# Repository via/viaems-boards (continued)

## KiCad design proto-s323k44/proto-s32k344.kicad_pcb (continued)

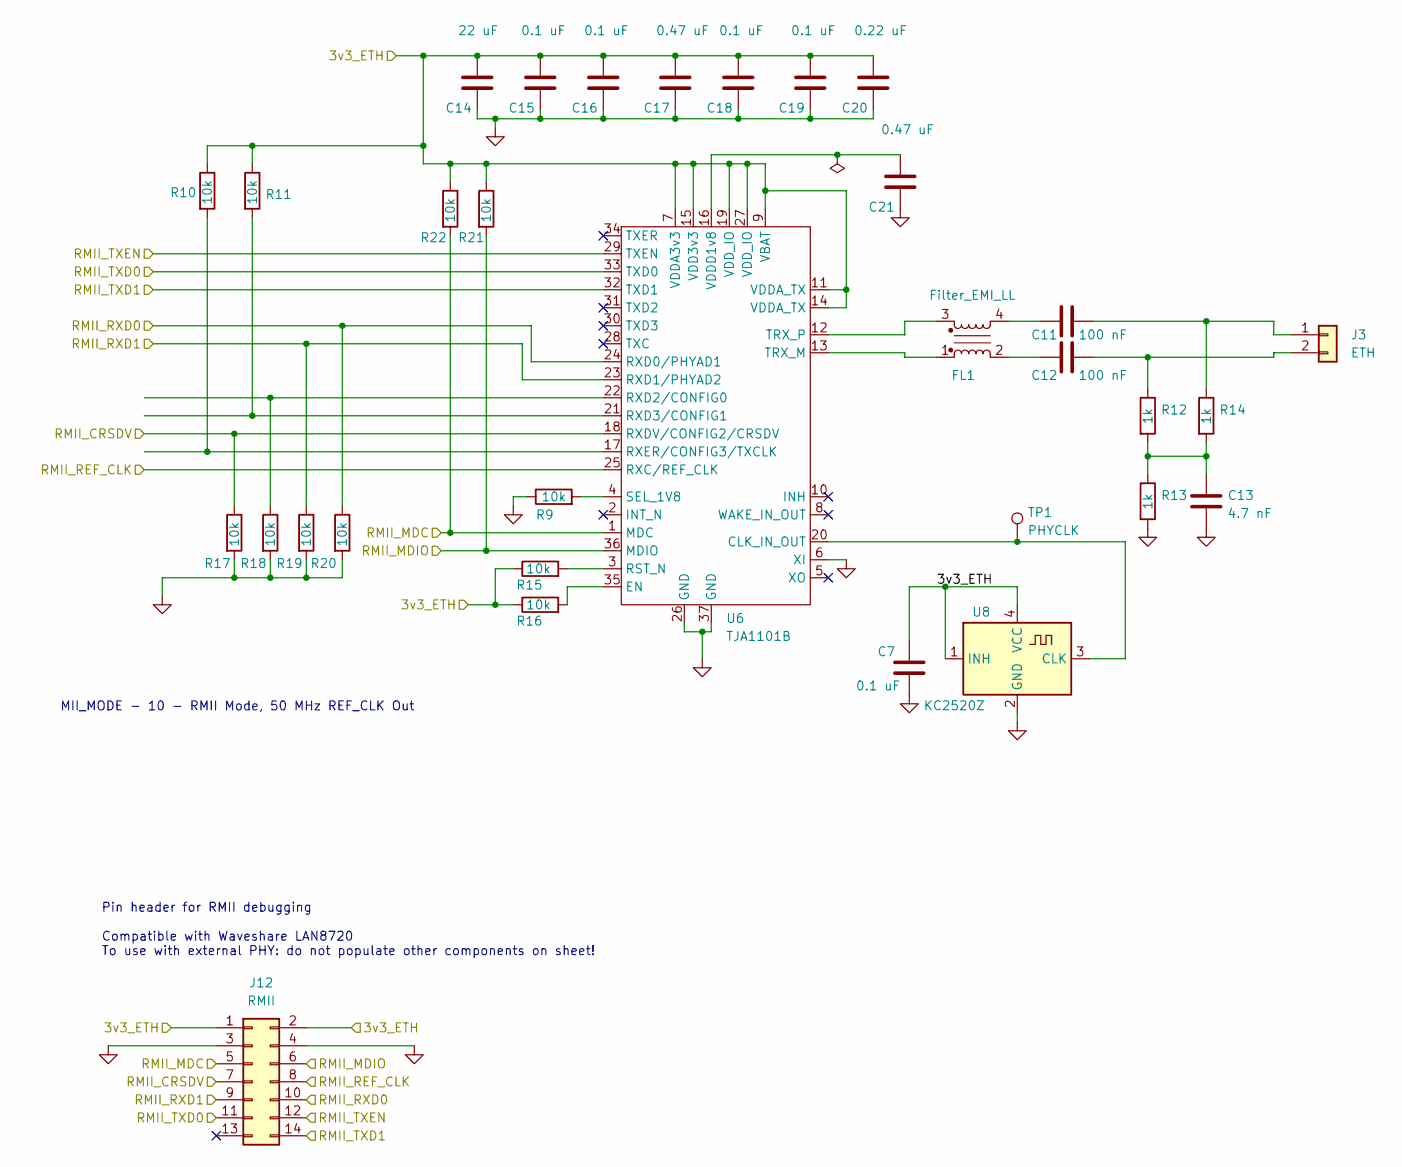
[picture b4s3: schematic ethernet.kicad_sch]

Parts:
C7, C15, C16, C18, C19: 0.1 uF; C_0805_2012Metric
C11, C12: 100 nF; C_0805_2012Metric
C13: 4.7 nF; C_0805_2012Metric
C14: 22 uF; C_0805_2012Metric
C17, C21: 0.47 uF; C_0805_2012Metric
C20: 0.22 uF; C_0805_2012Metric
FL1: Filter_EMI_LL; DLW43_MUR; Digikey-Part DLW43MH201XK2L
J3: ETH; PinHeader_1x02_P2.54mm_Vertical
J12: RMII; PinHeader_2x07_P2.54mm_Vertical
R9, R10, R11, R15, R16, R17, R18, R19, R20, R21, R22: 10k; R_0805_2012Metric
R12, R13, R14: 1k; R_0805_2012Metric
TP1: PHYCLK; TestPoint_Pad_D1.5mm
U6: TJA1101B; QFN-36-1EP_6x6mm_P0.5mm_EP3.7x3.7mm
U8: KC2520Z; Oscillator_SMD_Kyocera_KC2520Z-4Pin_2.5x2.0mm

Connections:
/3v3: C7.1, C14.1, C15.1, C16.1, C17.1, C18.1, C19.1, C20.1, J12.1, J12.2, R10.1, R11.1, R15.1, R16.1, R21.1, R22.1, U6.7 (VDDA3v3), U6.9 (VBAT), U6.11 (VDDA_TX), U6.14 (VDDA_TX), U6.15 (VDD3v3), U6.19 (VDD_IO), U6.27 (VDD_IO), U8.1 (INH), U8.4 (VCC); also elsewhere on the board
/PTB4: J12.14, U6.32 (TXD1); also elsewhere on the board
/PTB5: J12.11, U6.33 (TXD0); also elsewhere on the board
/PTC0: J12.10, R20.1, U6.24 (RXD0/PHYAD1); also elsewhere on the board
/PTC1: J12.9, R19.1, U6.23 (RXD1/PHYAD2); also elsewhere on the board
/PTC17: J12.7, R17.1, U6.18 (RXDV/CONFIG2/CRSDV); also elsewhere on the board
/PTD6: J12.8, U6.25 (RXC/REF_CLK); also elsewhere on the board
/PTD16: J12.6, R21.2, U6.36 (MDIO); also elsewhere on the board
/PTE8: J12.5, R22.2, U6.1 (MDC); also elsewhere on the board
/PTE9: J12.12, U6.29 (TXEN); also elsewhere on the board
GND: C7.2, C13.2, C14.2, C15.2, C16.2, C17.2, C18.2, C19.2, C20.2, C21.2, J12.3, J12.4, R9.1, R13.2, R17.2, R18.2, R19.2, R20.2, U6.6 (XI), U6.26 (GND), U6.37 (GND), U8.2 (GND); also elsewhere on the board
unnamed: C11.1, FL1.4
unnamed: C12.1, FL1.2
unnamed: C13.1, R12.2, R13.1, R14.2
unnamed: C11.2, J3.1, R14.1
unnamed: C12.2, J3.2, R12.1
unnamed: TP1.1, U6.20 (CLK_IN_OUT), U8.3 (CLK)
unnamed: R16.2, U6.35 (EN)
unnamed: R15.2, U6.3 (RST_N)
unnamed: R18.1, U6.22 (RXD2/CONFIG0)
unnamed: R11.2, U6.21 (RXD3/CONFIG1)
unnamed: R10.2, U6.17 (RXER/CONFIG3/TXCLK)
unnamed: R9.2, U6.4 (SEL_1V8)
unnamed: FL1.1, U6.13 (TRX_M)
unnamed: FL1.3, U6.12 (TRX_P)
unnamed: C21.1, U6.16 (VDDD1v8)

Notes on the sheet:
MII_MODE - 10 - RMII Mode, 50 MHz REF_CLK Out
Pin header for RMII debugging Compatible with Waveshare LAN8720 To use with external PHY: do not populate other components on sheet!

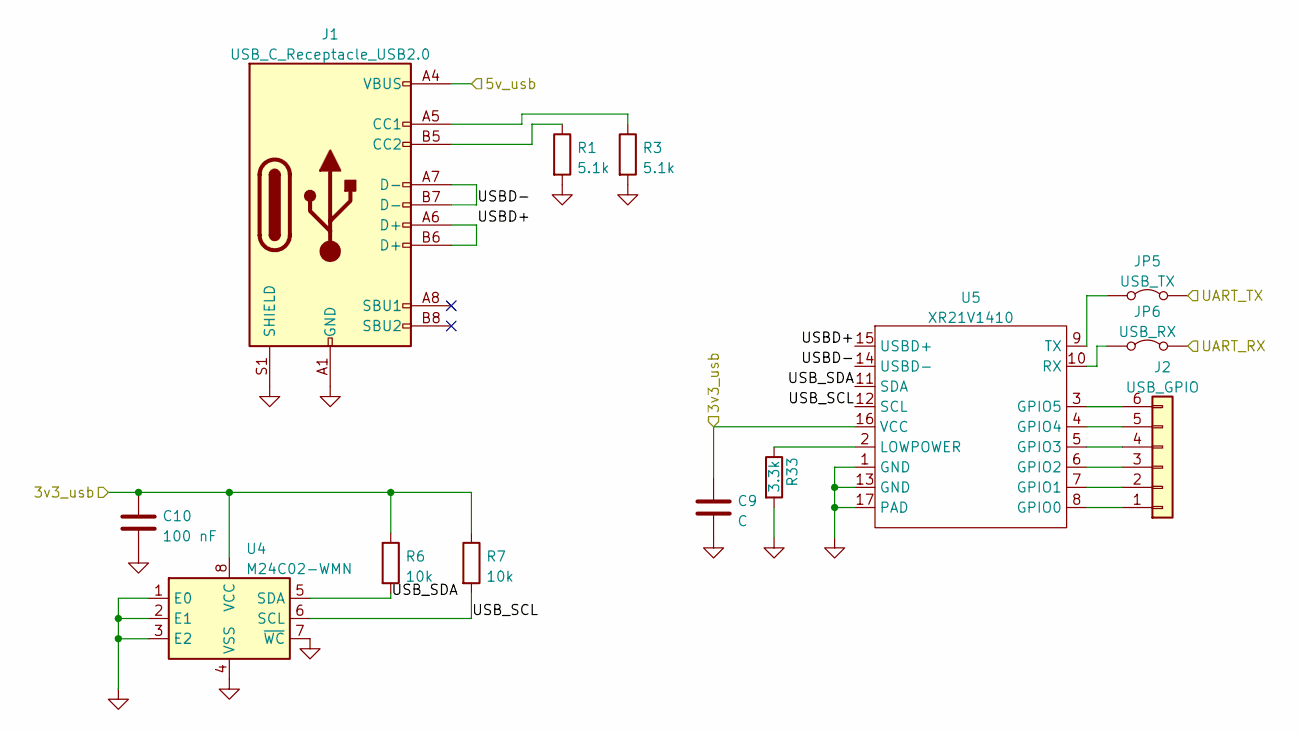
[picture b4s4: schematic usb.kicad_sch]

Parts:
C9: C; C_0805_2012Metric
C10: 100 nF; C_0805_2012Metric
J1: USB_C_Receptacle_USB2.0; USB_C_Receptacle_GCT_USB4105-xx-A_16P_TopMnt_Horizontal
J2: USB_GPIO; PinHeader_2x03_P2.54mm_Vertical
JP5: USB_TX; PinHeader_1x02_P2.54mm_Vertical
JP6: USB_RX; PinHeader_1x02_P2.54mm_Vertical
R1, R3: 5.1k; R_0805_2012Metric
R6, R7: 10k; R_0805_2012Metric
R33: 3.3k; R_0805_2012Metric
U4: M24C02-WMN; SOIC-8_3.9x4.9mm_P1.27mm
U5: XR21V1410; QFN-16-1EP_3x3mm_P0.5mm_EP1.7x1.7mm

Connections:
/3v3: C9.1, C10.1, R6.1, R7.1, U4.8 (VCC), U5.16 (VCC); also elsewhere on the board
/5v_usb: J1.A4 (VBUS), J1.A9 (VBUS), J1.B4 (VBUS), J1.B9 (VBUS); also elsewhere on the board
/PTC15: JP5.2 (B); also elsewhere on the board
/PTC16: JP6.2 (B); also elsewhere on the board
/USB/USBD+: J1.A6 (D+), J1.B6 (D+), U5.15 (USBD+)
/USB/USBD-: J1.A7 (D-), J1.B7 (D-), U5.14 (USBD-)
/USB/USB_SCL: R7.2, U4.6 (SCL), U5.12 (SCL)
/USB/USB_SDA: R6.2, U4.5 (SDA), U5.11 (SDA)
GND: C9.2, C10.2, J1.A1 (GND), J1.A12 (GND), J1.B1 (GND), J1.B12 (GND), J1.S1 (SHIELD), R1.2, R3.2, R33.2, U4.1 (E0), U4.2 (E1), U4.3 (E2), U4.4 (VSS), U4.7 (~WC), U5.1 (GND), U5.13 (GND), U5.17 (PAD); also elsewhere on the board
unnamed: J1.A5 (CC1), R3.1
unnamed: J1.B5 (CC2), R1.1
unnamed: J2.1, U5.8 (GPIO0)
unnamed: J2.2, U5.7 (GPIO1)
unnamed: J2.3, U5.6 (GPIO2)
unnamed: J2.4, U5.5 (GPIO3)
unnamed: J2.5, U5.4 (GPIO4)
unnamed: J2.6, U5.3 (GPIO5)
unnamed: JP5.1 (A), U5.9 (TX)
unnamed: JP6.1 (A), U5.10 (RX)
unnamed: R33.1, U5.2 (LOWPOWER)

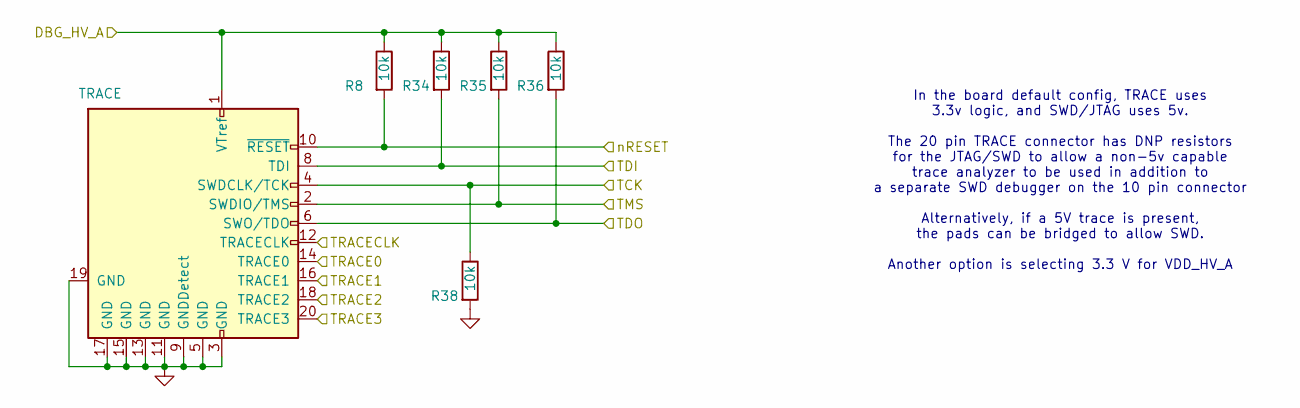
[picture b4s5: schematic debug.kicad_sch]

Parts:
J13: TRACE; PinSocket_2x10_P1.27mm_Vertical_SMD
R8, R34, R35, R36, R38: 10k; R_0805_2012Metric

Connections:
/PTA4: J13.2 (SWDIO/TMS), R35.2; also elsewhere on the board
/PTA5: J13.10 (~RESET), R8.2; also elsewhere on the board
/PTA10: J13.6 (SWO/TDO), R36.2; also elsewhere on the board
/PTC2: J13.12 (TRACECLK); also elsewhere on the board
/PTC4: J13.4 (SWDCLK/TCK), R38.1; also elsewhere on the board
/PTC5: J13.8 (TDI), R34.2; also elsewhere on the board
/PTD7: J13.14 (TRACE0); also elsewhere on the board
/PTD10: J13.20 (TRACE3); also elsewhere on the board
/PTD11: J13.18 (TRACE2); also elsewhere on the board
/PTD12: J13.16 (TRACE1); also elsewhere on the board
/VDD_HV_A: J13.1 (VTref), R8.1, R34.1, R35.1, R36.1; also elsewhere on the board
GND: J13.3 (GND), J13.5 (GND), J13.9 (GNDDetect), J13.11 (GND), J13.13 (GND), J13.15 (GND), J13.17 (GND), J13.19 (GND), R38.2; also elsewhere on the board

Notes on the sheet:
In the board default config, TRACE uses 3.3v logic, and SWD/JTAG uses 5v. The 20 pin TRACE connector has DNP resistors for the JTAG/SWD to allow a non-5v capable trace analyzer to be used in addition to a separate SWD debugger on the 10 pin connector Alternatively, if a 5V trace is present, the pad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

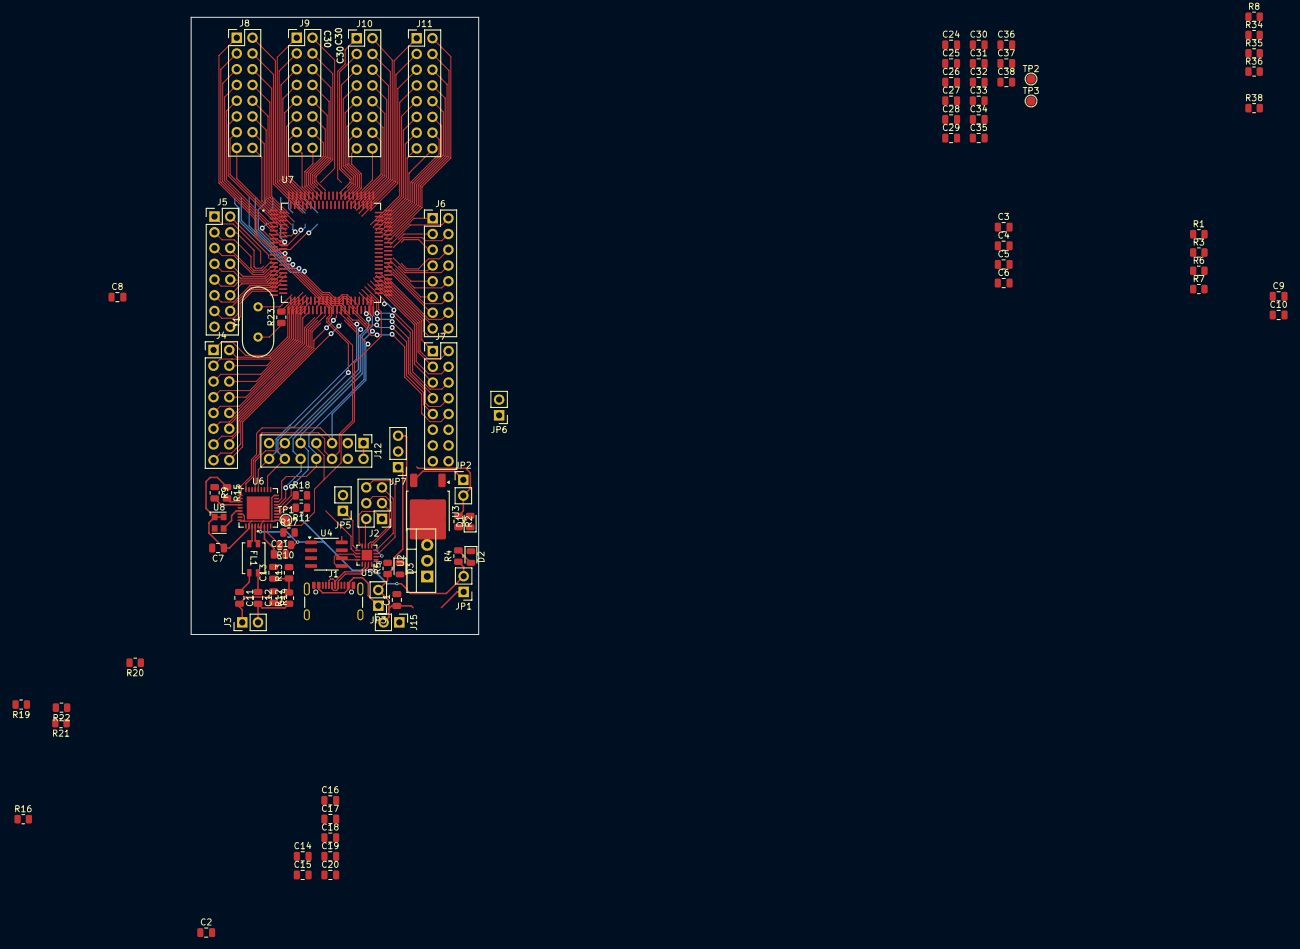
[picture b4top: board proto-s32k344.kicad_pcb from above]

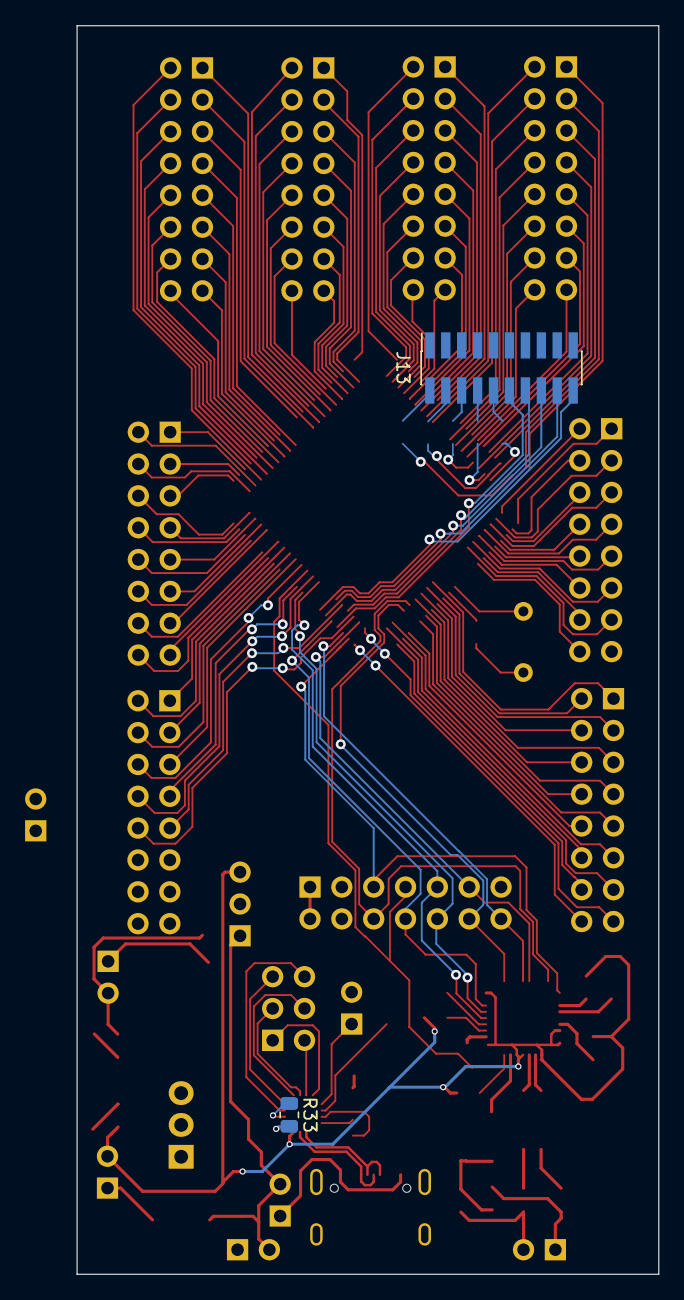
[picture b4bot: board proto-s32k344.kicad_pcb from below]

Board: 2 copper layers, 46.4 x 99.6 mm, 99 parts (2 on the bottom side), 190 nets.

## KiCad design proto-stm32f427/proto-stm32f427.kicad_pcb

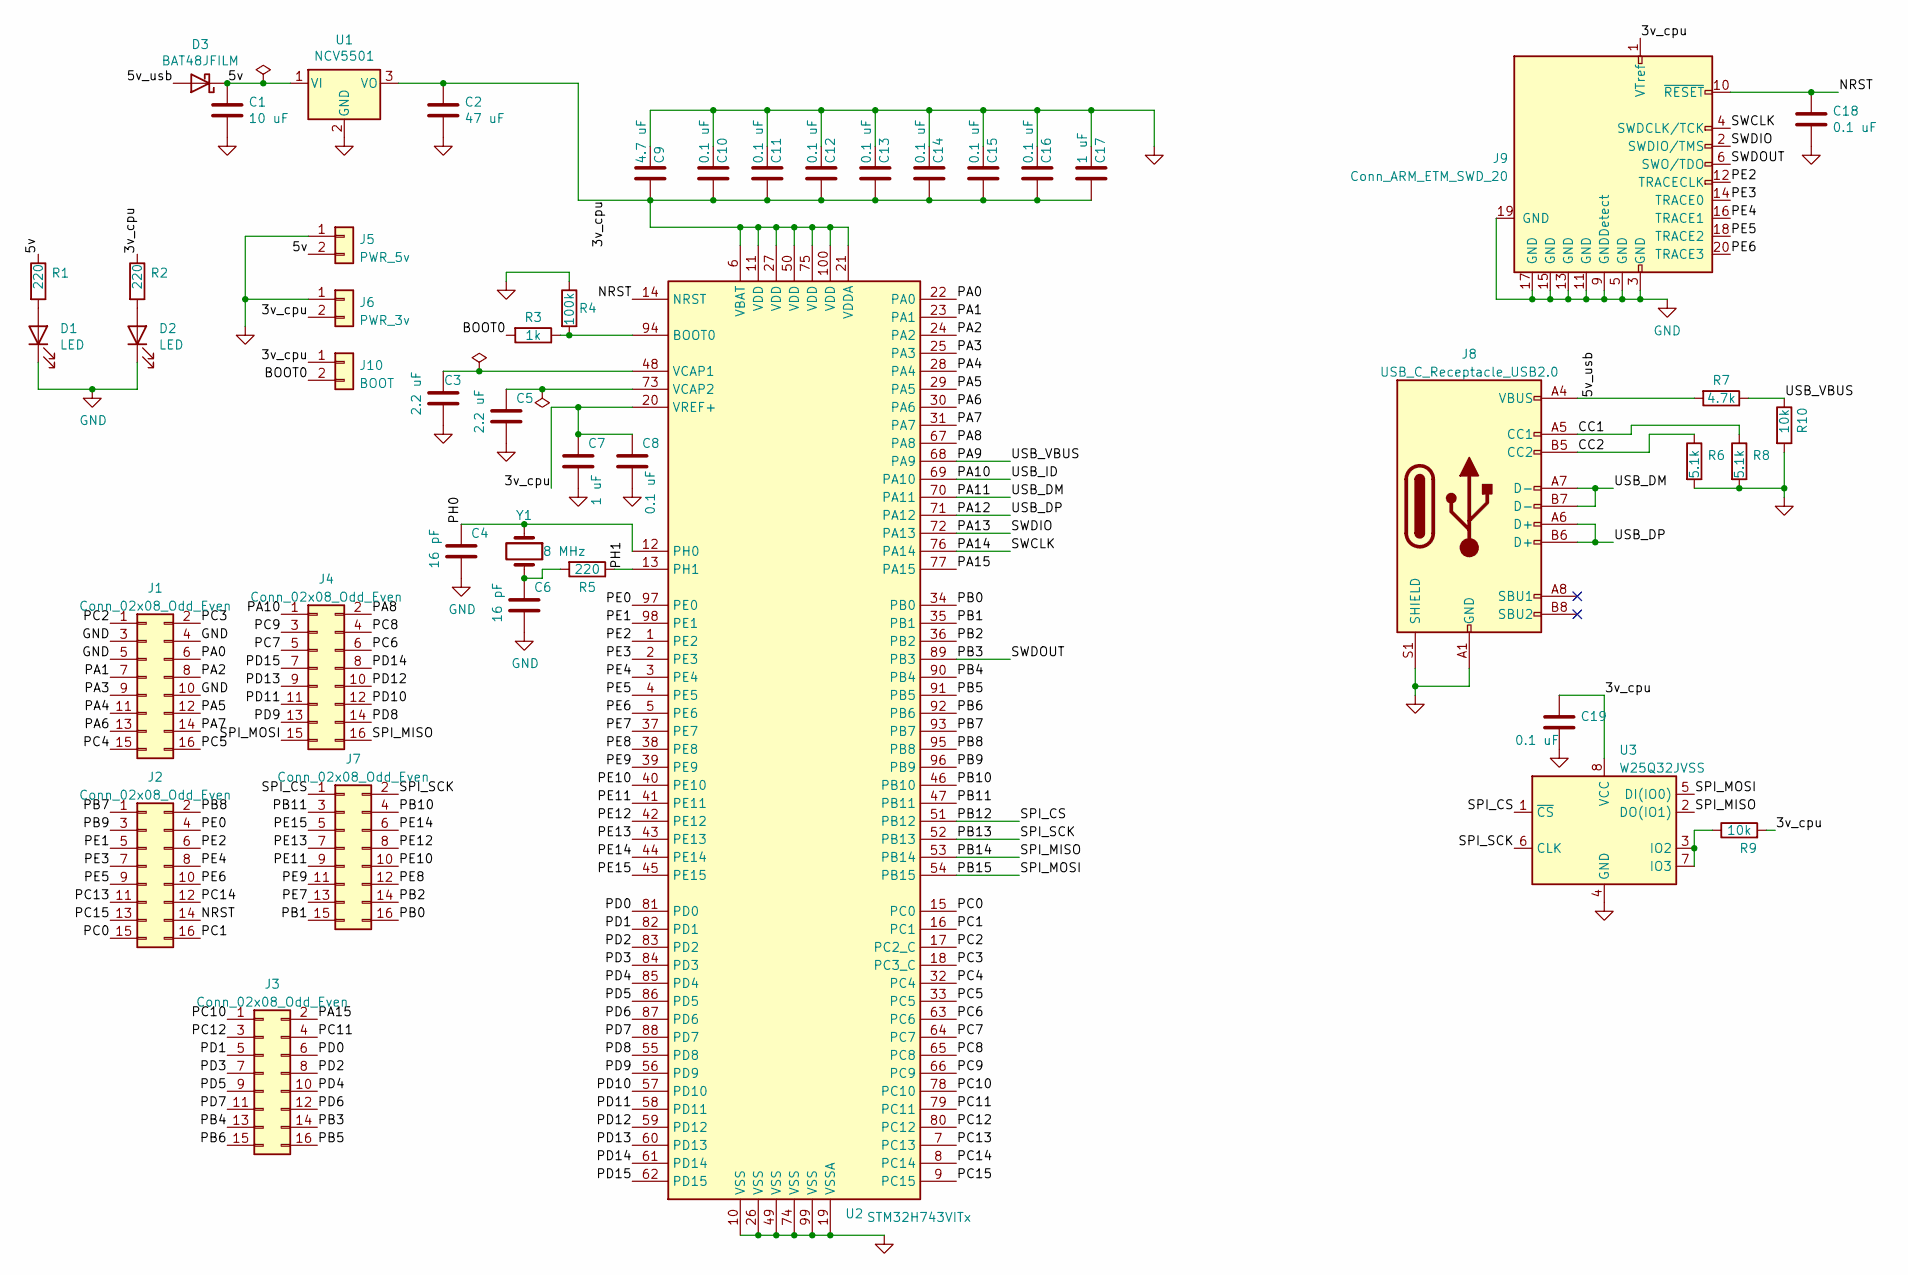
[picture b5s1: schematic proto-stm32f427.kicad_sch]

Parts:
C1: 10 uF; C_0805_2012Metric_Pad1.15x1.40mm_HandSolder; Digikey-Part 587-3417-1-ND
C2: 47 uF; C_0805_2012Metric_Pad1.15x1.40mm_HandSolder; Digikey-Part 718-1608-1-ND
C3, C5: 2.2 uF; C_0805_2012Metric_Pad1.15x1.40mm_HandSolder; Digikey-Part 1276-1188-1-ND
C4, C6: 16 pF; C_0805_2012Metric_Pad1.15x1.40mm_HandSolder; Digikey-Part 311-4228-1-ND
C7, C17: 1 uF; C_0805_2012Metric_Pad1.15x1.40mm_HandSolder; Digikey-Part 1276-1066-1-ND
C8, C10, C11, C12, C13, C14, C15, C16, C18: 0.1 uF; C_0805_2012Metric_Pad1.15x1.40mm_HandSolder; Digikey-Part 478-10836-1-ND
C9: 4.7 uF; C_0805_2012Metric_Pad1.15x1.40mm_HandSolder; Digikey-Part 445-14527-1-ND
C19: 0.1 uF; C_0805_2012Metric_Pad1.18x1.45mm_HandSolder
D1, D2: LED; LED_0805_2012Metric_Pad1.15x1.40mm_HandSolder; Digikey-Part 475-1415-1-ND
D3: BAT48JFILM; D_SOD-323_HandSoldering; Digikey-Part B0530WS-FDICT-ND
J1, J2, J3, J4, J7: Conn_02x08_Odd_Even; PinHeader_2x08_P2.54mm_Vertical
J5: PWR_5v; PinHeader_1x02_P2.54mm_Vertical
J6: PWR_3v; PinHeader_1x02_P2.54mm_Vertical
J8: USB_C_Receptacle_USB2.0; USB_C_Receptacle_GCT_USB4105-xx-A_16P_TopMnt_Horizontal; Digikey-Part 2073-USB4105-GF-ACT-ND
J9: Conn_ARM_ETM_SWD_20; PinHeader_2x10_P1.27mm_Vertical_SMD; Digikey-Part SAM9456-ND
J10: BOOT; PinHeader_1x02_P2.54mm_Vertical
R1, R2, R5: 220; R_0805_2012Metric_Pad1.20x1.40mm_HandSolder; Digikey-Part A129741CT-ND
R3: 1k; R_0805_2012Metric_Pad1.20x1.40mm_HandSolder; Digikey-Part RNCP0805FTD1K00CT-ND
R4: 100k; R_0805_2012Metric_Pad1.20x1.40mm_HandSolder; Digikey-Part P100KDACT-ND
R6, R8: 5.1k; R_0805_2012Metric_Pad1.20x1.40mm_HandSolder
R7: 4.7k; R_0805_2012Metric_Pad1.20x1.40mm_HandSolder; Digikey-Part 311-4.70KCRCT-ND
R9: 10k; R_0805_2012Metric_Pad1.20x1.40mm_HandSolder
R10: 10k; R_0805_2012Metric_Pad1.20x1.40mm_HandSolder; Digikey-Part RNCF0805DTE10K0CT-ND
U1: NCV5501; TO-252-2; Digikey-Part NCV5501DT33GOS-ND
U2: STM32H743VITx; LQFP-100_14x14mm_P0.5mm
U3: W25Q32JVSS; SOIC-8_5.23x5.23mm_P1.27mm
Y1: 8 MHz; Crystal_HC49-U_Vertical; Digikey-Part 535-10212-1-ND

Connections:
/3v_cpu: C2.1, C7.1, C8.1, C9.2, C10.2, C11.2, C12.2, C13.2, C14.2, C15.2, C16.2, C17.2, C19.1, J6.2, J9.1 (VTref), J10.1, R2.1, R9.2, U1.3 (VO), U2.6 (VBAT), U2.11 (VDD), U2.20 (VREF+), U2.21 (VDDA), U2.27 (VDD), U2.50 (VDD), U2.75 (VDD), U2.100 (VDD), U3.8 (VCC)
/5v: C1.1, D3.1 (K), J5.2, R1.1, U1.1 (VI)
/5v_usb: D3.2 (A), J8.A4 (VBUS), J8.A9 (VBUS), J8.B4 (VBUS), J8.B9 (VBUS), R7.2
/BOOT0: J10.2, R3.2
/CC1: J8.A5 (CC1), R8.1
/CC2: J8.B5 (CC2), R6.1
/NRST: C18.1, J2.14, J9.10 (~RESET), U2.14 (NRST)
/PA0: J1.6, U2.22 (PA0)
/PA1: J1.7, U2.23 (PA1)
/PA2: J1.8, U2.24 (PA2)
/PA3: J1.9, U2.25 (PA3)
/PA4: J1.11, U2.28 (PA4)
/PA5: J1.12, U2.29 (PA5)
/PA6: J1.13, U2.30 (PA6)
/PA7: J1.14, U2.31 (PA7)
/PA8: J4.2, U2.67 (PA8)
/PA9: R7.1, R10.1, U2.68 (PA9)
/PA10: J4.1, U2.69 (PA10)
/PA11: J8.A7 (D-), J8.B7 (D-), U2.70 (PA11)
/PA12: J8.A6 (D+), J8.B6 (D+), U2.71 (PA12)
/PA13: J9.2 (SWDIO/TMS), U2.72 (PA13)
/PA14: J9.4 (SWDCLK/TCK), U2.76 (PA14)
/PA15: J3.2, U2.77 (PA15)
/PB0: J7.16, U2.34 (PB0)
/PB1: J7.15, U2.35 (PB1)
/PB2: J7.14, U2.36 (PB2)
/PB3: J3.14, J9.6 (SWO/TDO), U2.89 (PB3)
/PB4: J3.13, U2.90 (PB4)
/PB5: J3.16, U2.91 (PB5)
/PB6: J3.15, U2.92 (PB6)
/PB7: J2.1, U2.93 (PB7)
/PB8: J2.2, U2.95 (PB8)
/PB9: J2.3, U2.96 (PB9)
/PB10: J7.4, U2.46 (PB10)
/PB11: J7.3, U2.47 (PB11)
/PB12: J7.1, U2.51 (PB12), U3.1 (~CS)
/PB13: J7.2, U2.52 (PB13), U3.6 (CLK)
/PB14: J4.16, U2.53 (PB14), U3.2 (DO(IO1))
/PB15: J4.15, U2.54 (PB15), U3.5 (DI(IO0))
/PC0: J2.15, U2.15 (PC0)
/PC1: J2.16, U2.16 (PC1)
/PC2: J1.1, U2.17 (PC2_C)
/PC3: J1.2, U2.18 (PC3_C)
/PC4: J1.15, U2.32 (PC4)
/PC5: J1.16, U2.33 (PC5)
/PC6: J4.6, U2.63 (PC6)
/PC7: J4.5, U2.64 (PC7)
/PC8: J4.4, U2.65 (PC8)
/PC9: J4.3, U2.66 (PC9)
/PC10: J3.1, U2.78 (PC10)
/PC11: J3.4, U2.79 (PC11)
/PC12: J3.3, U2.80 (PC12)
/PC13: J2.11, U2.7 (PC13)
/PC14: J2.12, U2.8 (PC14)
/PC15: J2.13, U2.9 (PC15)
/PD0: J3.6, U2.81 (PD0)
/PD1: J3.5, U2.82 (PD1)
/PD2: J3.8, U2.83 (PD2)
/PD3: J3.7, U2.84 (PD3)
/PD4: J3.10, U2.85 (PD4)
/PD5: J3.9, U2.86 (PD5)
/PD6: J3.12, U2.87 (PD6)
/PD7: J3.11, U2.88 (PD7)
/PD8: J4.14, U2.55 (PD8)
/PD9: J4.13, U2.56 (PD9)
/PD10: J4.12, U2.57 (PD10)
/PD11: J4.11, U2.58 (PD11)
/PD12: J4.10, U2.59 (PD12)
/PD13: J4.9, U2.60 (PD13)
/PD14: J4.8, U2.61 (PD14)
/PD15: J4.7, U2.62 (PD15)
/PE0: J2.4, U2.97 (PE0)
/PE1: J2.5, U2.98 (PE1)
/PE2: J2.6, J9.12 (TRACECLK), U2.1 (PE2)
/PE3: J2.7, J9.14 (TRACE0), U2.2 (PE3)
/PE4: J2.8, J9.16 (TRACE1), U2.3 (PE4)
/PE5: J2.9, J9.18 (TRACE2), U2.4 (PE5)
/PE6: J2.10, J9.20 (TRACE3), U2.5 (PE6)
/PE7: J7.13, U2.37 (PE7)
/PE8: J7.12, U2.38 (PE8)
/PE9: J7.11, U2.39 (PE9)
/PE10: J7.10, U2.40 (PE10)
/PE11: J7.9, U2.41 (PE11)
/PE12: J7.8, U2.42 (PE12)
/PE13: J7.7, U2.43 (PE13)
/PE14: J7.6, U2.44 (PE14)
/PE15: J7.5, U2.45 (PE15)
/PH0: C4.2, U2.12 (PH0), Y1.1
/PH1: R5.1, U2.13 (PH1)
GND: C1.2, C2.2, C3.2, C4.1, C5.2, C6.1, C7.2, C8.2, C9.1, C10.1, C11.1, C12.1, C13.1, C14.1, C15.1, C16.1, C17.1, C18.2, C19.2, D1.1 (K), D2.1 (K), J1.3, J1.4, J1.5, J1.10, J5.1, J6.1, J8.A1 (GND), J8.A12 (GND), J8.B1 (GND), J8.B12 (GND), J8.S1 (SHIELD), J9.3 (GND), J9.5 (GND), J9.9 (GNDDetect), J9.11 (GND), J9.13 (GND), J9.15 (GND), J9.17 (GND), J9.19 (GND), R4.1, R6.2, R8.2, R10.2, U1.2 (GND), U2.10 (VSS), U2.19 (VSSA), U2.26 (VSS), U2.49 (VSS), U2.74 (VSS), U2.99 (VSS), U3.4 (GND)
unnamed: C3.1, U2.48 (VCAP1)
unnamed: C5.1, U2.73 (VCAP2)
unnamed: C6.2, R5.2, Y1.2
unnamed: D1.2 (A), R1.2
unnamed: D2.2 (A), R2.2
unnamed: R3.1, R4.2, U2.94 (BOOT0)
unnamed: R9.1, U3.3 (IO2), U3.7 (IO3)

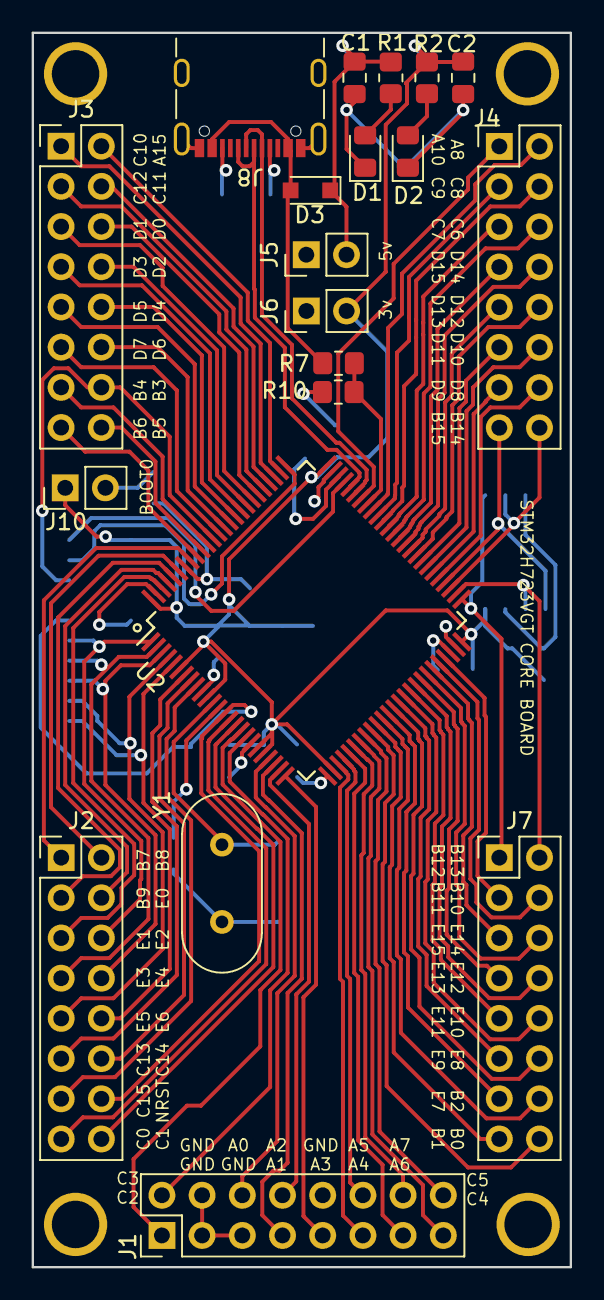
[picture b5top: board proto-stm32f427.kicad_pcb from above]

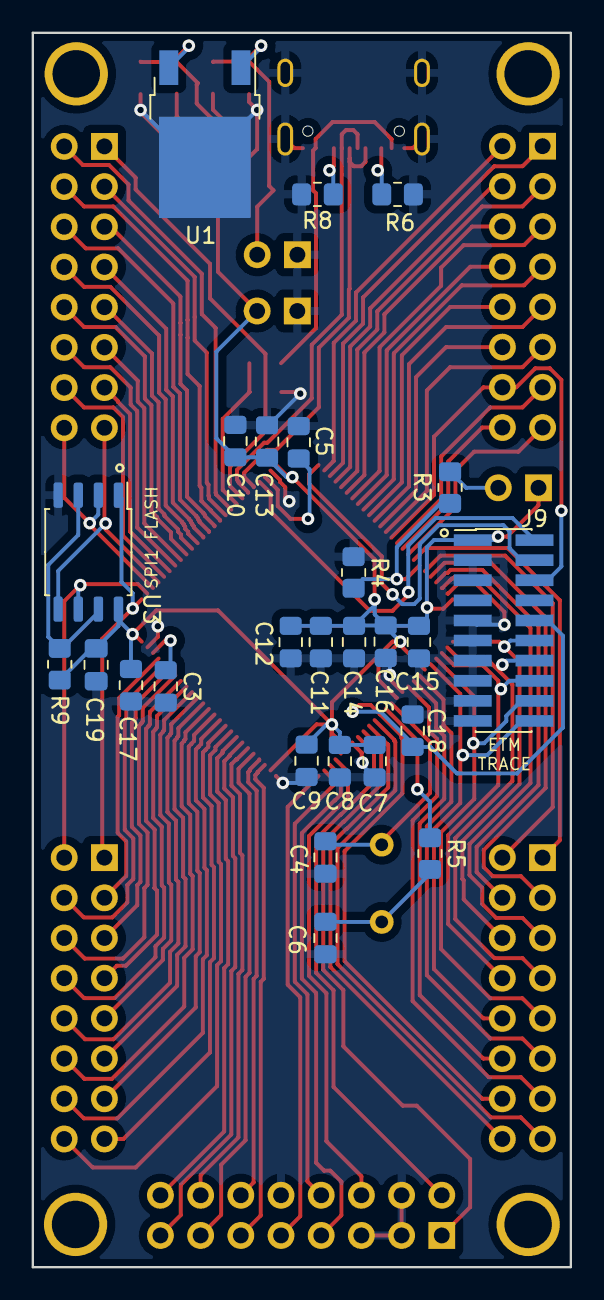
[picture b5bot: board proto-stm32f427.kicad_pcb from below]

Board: 2 copper layers, 34.0 x 78.0 mm, 46 parts (26 on the bottom side), 97 nets.

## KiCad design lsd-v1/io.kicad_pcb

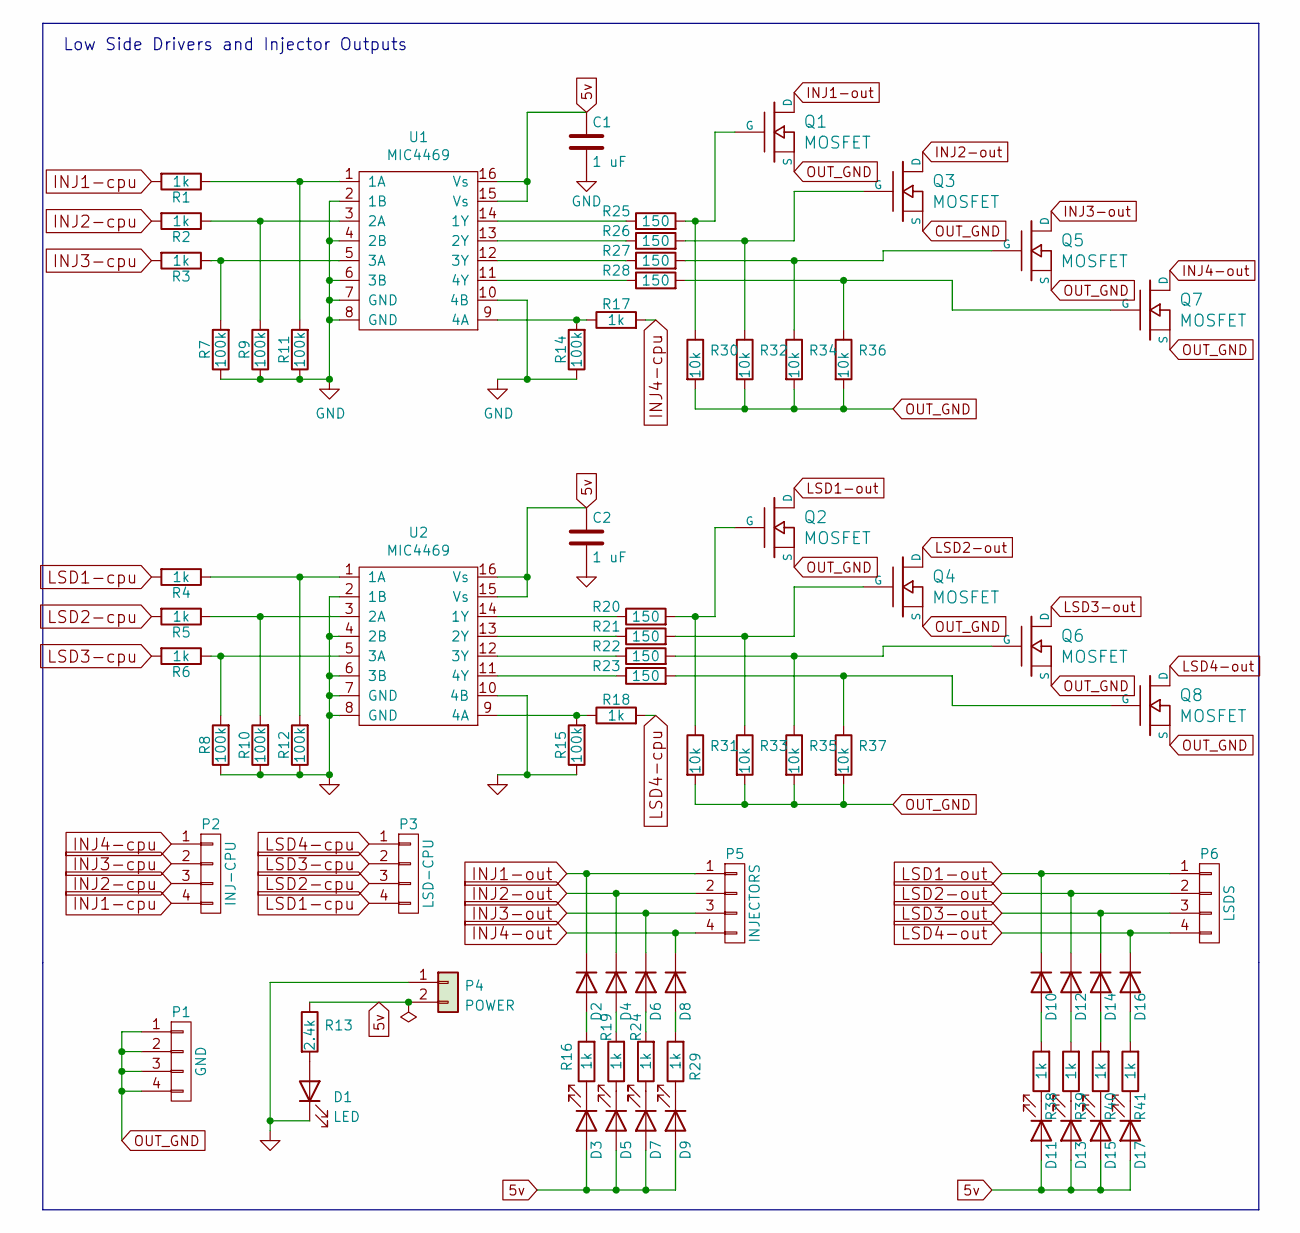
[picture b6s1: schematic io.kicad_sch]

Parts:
C1, C2: 1 uF; C_0805_2012Metric_Pad1.18x1.45mm_HandSolder
D1: LED; LED_0805_2012Metric
D2, D4, D6, D8, D10, D12, D14, D16: 1N4148; D_0805_2012Metric_Pad1.15x1.40mm_HandSolder
D3, D5, D7, D9, D11, D13, D15, D17: LED; LED_0805_2012Metric_Pad1.15x1.40mm_HandSolder
P1: GND; PinHeader_2x02_P2.54mm_Vertical
P2: INJ-CPU; PinHeader_1x04_P2.54mm_Vertical
P3: LSD-CPU; PinHeader_1x04_P2.54mm_Vertical
P4: POWER; PinHeader_1x02_P2.54mm_Vertical
P5: INJECTORS; PinHeader_1x04_P2.54mm_Vertical
P6: LSDS; PinHeader_1x04_P2.54mm_Vertical
Q1, Q2, Q3, Q4, Q5, Q6, Q7, Q8: MOSFET; TO-252-2
R1, R2, R3, R4, R5, R6, R16, R17, R18, R19, R24, R29, R38, R39, R40, R41: 1k; R_0805_2012Metric_Pad1.20x1.40mm_HandSolder
R7, R8, R9, R10, R11, R12, R14, R15: 100k; R_0805_2012Metric_Pad1.20x1.40mm_HandSolder
R13: 2.4k; R_0805_2012Metric_Pad1.20x1.40mm_HandSolder
R20, R21, R22, R23, R25, R26, R27, R28: 150; R_0805_2012Metric_Pad1.20x1.40mm_HandSolder
R30, R31, R32, R33, R34, R35, R36, R37: 10k; R_0805_2012Metric_Pad1.20x1.40mm_HandSolder
U1, U2: MIC4469; SOIC-16W_7.5x10.3mm_P1.27mm

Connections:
5v: C1.1, C2.1, D3.2 (A), D5.2 (A), D7.2 (A), D9.2 (A), D11.2 (A), D13.2 (A), D15.2 (A), D17.2 (A), P4.2, R13.1, U1.15 (Vs), U1.16 (Vs), U2.15 (Vs), U2.16 (Vs)
GND: C1.2, C2.2, D1.1 (K), P4.1, R7.1, R8.1, R9.1, R10.1, R11.1, R12.1, R14.1, R15.1, U1.2 (1B), U1.4 (2B), U1.6 (3B), U1.7 (GND), U1.8 (GND), U1.10 (4B), U2.2 (1B), U2.4 (2B), U2.6 (3B), U2.7 (GND), U2.8 (GND), U2.10 (4B)
INJ1-cpu: P2.4, R1.2
INJ1-out: D2.1 (K), P5.1, Q1.2 (D)
INJ2-cpu: P2.3, R2.2
INJ2-out: D4.1 (K), P5.2, Q3.2 (D)
INJ3-cpu: P2.2, R3.2
INJ3-out: D6.1 (K), P5.3, Q5.2 (D)
INJ4-cpu: P2.1, R17.2
INJ4-out: D8.1 (K), P5.4, Q7.2 (D)
LSD1-cpu: P3.4, R4.2
LSD1-out: D10.1 (K), P6.1, Q2.2 (D)
LSD2-cpu: P3.3, R5.2
LSD2-out: D12.1 (K), P6.2, Q4.2 (D)
LSD3-cpu: P3.2, R6.2
LSD3-out: D14.1 (K), P6.3, Q6.2 (D)
LSD4-cpu: P3.1, R18.2
LSD4-out: D16.1 (K), P6.4, Q8.2 (D)
unnamed: D1.2 (A), R13.2
unnamed: D2.2 (A), R16.2
unnamed: D3.1 (K), R16.1
unnamed: D4.2 (A), R19.2
unnamed: D5.1 (K), R19.1
unnamed: D6.2 (A), R24.2
unnamed: D7.1 (K), R24.1
unnamed: D8.2 (A), R29.2
unnamed: D9.1 (K), R29.1
unnamed: D10.2 (A), R38.2
unnamed: D11.1 (K), R38.1
unnamed: D12.2 (A), R39.2
unnamed: D13.1 (K), R39.1
unnamed: D14.2 (A), R40.2
unnamed: D15.1 (K), R40.1
unnamed: D16.2 (A), R41.2
unnamed: D17.1 (K), R41.1
unnamed: Q1.1 (G), R25.2, R30.1
unnamed: Q2.1 (G), R20.2, R31.1
unnamed: Q3.1 (G), R26.2, R32.1
unnamed: Q4.1 (G), R21.2, R33.1
unnamed: Q5.1 (G), R27.2, R34.1
unnamed: Q6.1 (G), R22.2, R35.1
unnamed: Q7.1 (G), R28.2, R36.1
unnamed: Q8.1 (G), R23.2, R37.1
unnamed: R1.1, R11.2, U1.1 (1A)
unnamed: R2.1, R9.2, U1.3 (2A)
unnamed: R3.1, R7.2, U1.5 (3A)
unnamed: R6.1, R8.2, U2.5 (3A)
unnamed: R5.1, R10.2, U2.3 (2A)
unnamed: R4.1, R12.2, U2.1 (1A)
unnamed: R14.2, R17.1, U1.9 (4A)
unnamed: R15.2, R18.1, U2.9 (4A)
unnamed: R20.1, U2.14 (1Y)
unnamed: R21.1, U2.13 (2Y)
unnamed: R22.1, U2.12 (3Y)
unnamed: R23.1, U2.11 (4Y)
unnamed: R25.1, U1.14 (1Y)
unnamed: R26.1, U1.13 (2Y)
unnamed: R27.1, U1.12 (3Y)
unnamed: R28.1, U1.11 (4Y)
OUT_GND: P1.1, P1.2, P1.3, P1.4, Q1.3 (S), Q2.3 (S), Q3.3 (S), Q4.3 (S), Q5.3 (S), Q6.3 (S), Q7.3 (S), Q8.3 (S), R30.2, R31.2, R32.2, R33.2, R34.2, R35.2, R36.2, R37.2

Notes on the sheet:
Low Side Drivers and Injector Outputs

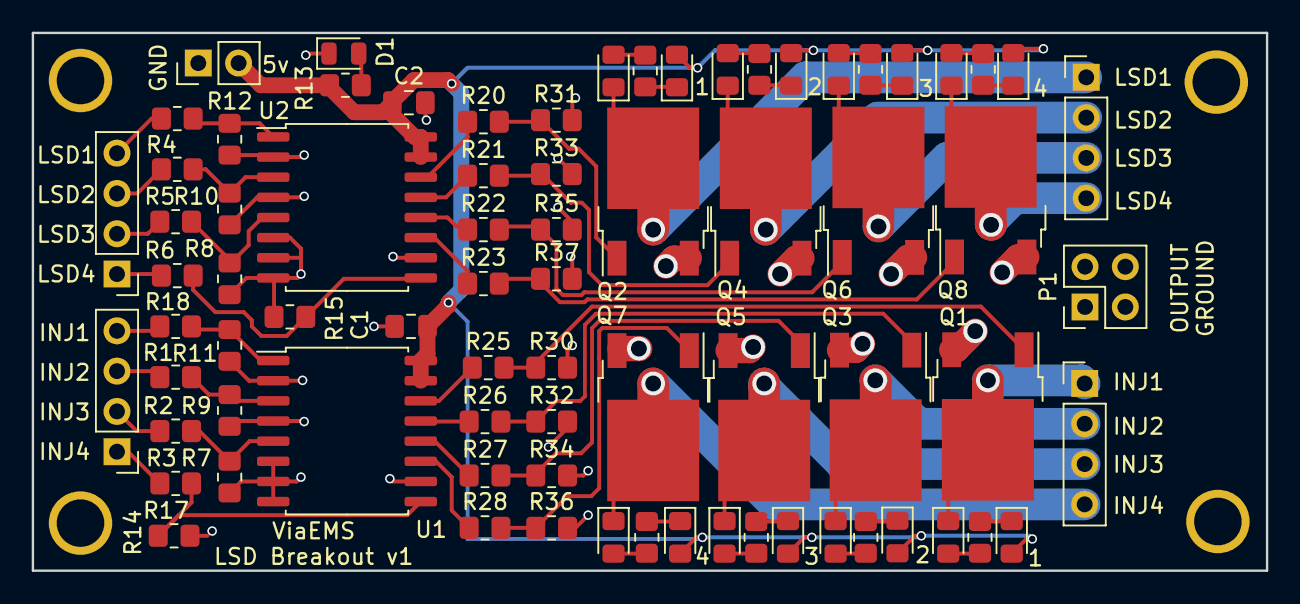
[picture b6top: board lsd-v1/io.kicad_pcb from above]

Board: 2 copper layers, 77.8 x 33.9 mm, 76 parts (0 on the bottom side), 60 nets.
